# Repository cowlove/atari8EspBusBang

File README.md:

# Atari 8-bit ESP32 BusBang

```text
@@@@@@@@@@@@@@@@@@@@@@@@@@@@@@@@@@@@@@@@@@@@@@@@@@@@@@@@@@@@@@@@@@@@@@@@@@@@@@@
@     _   _             _  ___  _     _ _        _____ ____  ____ _________   @
@    / \ | |_ __ _ _ __(_)( _ )| |__ (_) |_     | ____/ ___||  _ \___ /___ \  @
@   / _ \| __/ _` | '__| |/ _ \| '_ \| | __|    |  _| \___ \| |_) ||_ \ __) | @
@  / ___ \ || (_| | |  | | (_) | |_) | | |_     | |___ ___) |  __/___) / __/  @
@ /_/   \_\__\__,_|_|  |_|\___/|_.__/|_|\__|    |_____|____/|_|  |____/_____| @
@                ____            ____                    _ _ _ _              @
@               | __ ) _   _ ___| __ )  __ _ _ __   __ _| | | | |             @
@               |  _ \| | | / __|  _ \ / _` | '_ \ / _` | | | | |             @
@               | |_) | |_| \__ \ |_) | (_| | | | | (_| |_|_|_|_|             @
@               |____/ \__,_|___/____/ \__,_|_| |_|\__, (_|_|_|_)             @
@                                                  |___/                      @
@@@@@@@@@@@@@@@@@@@@@@@@@@@@@@@@@@@@@@@@@@@@@@@@@@@@@@@@@@@@@@@@@@@@@@@@@@@@@@@
READY
█
```

## About the Project

Atari8EspBusBang uses a naked ESP32-S3 dev board to bit-bang the Atari 8-bit memory bus through the PBI port. The ESP32 has enough speed to handle the 6502's memory requests, overriding base memory and emulating extended memory, multi-bank cartridges, and SIO devices.  It implements a true software-defined PBI device.  The outside world, modern ideas, and high-level code all have direct access to the stock Atari system and memory at 960MB/sec.  

This started as a bus monitor for troubleshooting a flaky 800XL. Once it became clear that the ESP32 could also *respond* to bus requests, the project grew into a software-defined PBI device— and an ultimate extreme performance exercise on the ESP32. The bus-protocol loop runs bare-metal on the ESP32's second core; the first core handles utility tasks such as networking, PBI device logic, and flash disk-image access.

This idea pushes the ESP32 to its absolute performance limit, and the lower level parts of the project are intricate.  I'd like to eventually implement a simple module interface for adding functionality and trying ideas in easy code steps without needing to mess with or understand the low-level internals of this project.  

## Building the Hardware

The KiCad designs, parts list, PCB ordering notes, and assembly notes are in the [hardware README](hardware/README.md).  Total cost is about $20, and requires only through-hole soldering of headers. 

## Building the Firmware

The project depends on a specific pinned and lightly patched version of ESP-IDF v6.1, llvm-mos-sdk, and a few other tools.  Using the provided docker image is probably the easiest way to arrange for this. 

```
./tools/container/setup-build-env.sh container-runtime    # Install software needed to run podman  
./tools/container/container.sh pull                       # fetch/build docker image (6Gb/5min)
./tools/container/container.sh flash_spiffs /dev/ttyACM0  # first-time init of flash storage
./tools/container/container.sh flash /dev/ttyACM0         # build firmware and flash esp32 
```

Or you can install this all directly on your system and run esp-idf tools directly.  
```
./tools/container/setup-build-env.sh          # installs patched esp-idf,etc in ~/opt/ (6Gb/5min)
. ~/opt/atari8esp-idf-v6.1/export.sh          # set env to run esp-idf tools
./tools/flash_spiffs -p /dev/ttyACM0          # first-time init of flash storage 
idf.py --ccache flash -p /dev/ttyACM0         # build firmware and flash esp32
```

For the pinned Podman build environment, see [`tools/container/container.sh`](tools/container/container.sh) and [its README](tools/container/README.md).

## Contributing

Bug reports and focused contributions are welcome.  Please report issues with the environment setup scripts. 

## License

Distributed under GPL-2.0. See [LICENSE.txt](LICENSE.txt).

## Contact

Jim Evans — [jim@vheavy.com](mailto:jim@vheavy.com)

Project repository: <https://github.com/cowlove/atari8EspBusBang>

Project webpage: <http://cowlove.com/atari8EspBusBang/>

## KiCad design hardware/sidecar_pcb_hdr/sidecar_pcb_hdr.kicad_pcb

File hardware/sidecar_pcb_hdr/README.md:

# sidecar_pcb_hdr: one Sidecar board for every Atari, on a 2x25 bus header (draft)

The bare-module Sidecar board ([sidecar_pcb_xe](../sidecar_pcb_xe/)'s
layout, [sidecar_pcb_xl](../sidecar_pcb_xl/)'s circuit), with the
machine-specific edge connector replaced by a **2x25, 2.54 mm SMD socket**
(J1). A small adapter per machine plugs into it:

| Adapter | Machine | Its connector |
|---|---|---|
| [bus_adapter_pbi](../bus_adapter_pbi/) | 600XL, 800XL | the PBI card-edge socket (5530843-5), which the XL board carried |
| [bus_adapter_eci](../bus_adapter_eci/) | 130XE, 65XE | the cartridge + ECI fingers, which the XE board carried |

Why: one main board for both machine families (the XE board never got the
2026-11-18 re-spin; this one has it), no gold fingers or 50-way card-edge
socket on every spin of the expensive board, and insertion force and wear
go to a cheap part.

**Status: generated and autorouted, not reviewed.** A starting point.

## The bus header

`../tools/bus_header.py` holds the pinout; every generator imports it.
Header pin n is PBI pin n for every signal, so the PBI adapter is a straight
pass-through and this board keeps the XL board's net on each pin. The PBI's
three NC pins are GND on the header (12 grounds instead of 9). EXTDEC, CAS
and RAS pass through from the PBI and are open on the ECI adapter. Nothing
on this board uses them.

| Pin | Signal | Pin | Signal |
|---|---|---|---|
| 1 | GND | 2 | EXTSEL |
| 3 | A0 | 4 | A1 |
| 5 | A2 | 6 | A3 |
| 7 | A4 | 8 | A5 |
| 9 | A6 | 10 | GND |
| 11 | A7 | 12 | A8 |
| 13 | A9 | 14 | A10 |
| 15 | A11 | 16 | A12 |
| 17 | A13 | 18 | A14 |
| 19 | GND | 20 | A15 |
| 21 | D0 | 22 | D1 |
| 23 | D2 | 24 | D3 |
| 25 | D4 | 26 | D5 |
| 27 | D6 | 28 | D7 |
| 29 | GND | 30 | GND |
| 31 | PHI2 | 32 | GND |
| 33 | GND (PBI NC) | 34 | RESET |
| 35 | IRQ | 36 | READY |
| 37 | GND (PBI NC) | 38 | EXTDEC |
| 39 | GND (PBI NC) | 40 | REFRESH |
| 41 | CAS | 42 | GND |
| 43 | MPD | 44 | RAS |
| 45 | GND | 46 | READ |
| 47 | VCC50 | 48 | VCC50 |
| 49 | AUDIO | 50 | GND |

On this board, 47 is `VCC50_1` (to J6, as on the XL board) and 48 is
`VCC50_2` (unused). On the adapters, both are the Atari's 5 V.

## Mechanics

- **The stack.** The adapter stands in the Atari's connector. Its header
  (through-hole) is on its front face, and this board mates parallel to it,
  with J1 on this board's back. The modules face away from the Atari and the
  antennas point up, as on the XL board. `make_sidecar_hdr_pcb.py` turns
  J1 so that, seen from the front, socket pin n lies over header pin n on
  both adapters (it compares pad patterns and fails if none fits).
- **Position.** J1 is centred on a strip added below the XE board's body,
  so the board is 96 x 49 mm and the lower left corner is empty. The stack
  height (about 8.5 mm with a standard socket and header) and the fit
  behind each machine are unchecked.
- **Still to decide:**
  - **Keying.** Plain pins can be plugged in reversed or one row off, with
    5 V on the header. Options: a shrouded header on the adapters (the SMD
    socket must then fit inside the shroud), or a key pin (a header pin
    clipped and its socket hole plugged).
  - **Hold-downs.** The socket now carries the board's weight and every
    USB-C insertion at J9. Choose a socket part with pegs or board locks.
  - **Pitch.** 2.54 mm is cheap and sturdy. 2.0 mm would save about 12 mm
    of strip.

## Files

| File | |
|---|---|
| `sidecar_pcb_hdr.kicad_sch` | Generated by [`../tools/make_sidecar_hdr_schematic.py`](../tools/make_sidecar_hdr_schematic.py) from an XL schematic built with `--sidecar-usbc`: don't edit by hand |
| `sidecar_pcb_hdr.kicad_pcb` | Built by [`../tools/make_sidecar_hdr_pcb.py`](../tools/make_sidecar_hdr_pcb.py) from the XE board (all of its placement, J1 replaced, new outline), then autorouted |
| `sidecar_pcb_hdr.kicad_pro`, `.kicad_dru` | The project (copied from the XE board), and the XE board's J9 rule |

To rebuild (see [../AGENTS.md](../AGENTS.md)):

```
S=$(mktemp -d)
kicad-cli sch export netlist -o $S/sc.net hardware/espBusBangSidecar/espBusBangSidecar.kicad_sch
python3 hardware/tools/make_sidecar_xl_schematic.py hardware/espBusBangSidecar/espBusBangSidecar.kicad_sch \
    $S/sc.net hardware/symbols $S/xl-usbc.kicad_sch --sidecar-usbc
kicad-cli sch export netlist -o $S/xl-usbc.net $S/xl-usbc.kicad_sch
python3 hardware/tools/make_sidecar_hdr_schematic.py $S/xl-usbc.kicad_sch $S/xl-usbc.net \
    hardware/symbols hardware/sidecar_pcb_hdr/sidecar_pcb_hdr.kicad_sch
kicad-cli sch export netlist -o $S/hdr.net hardware/sidecar_pcb_hdr/sidecar_pcb_hdr.kicad_sch
(cd hardware/tools && /usr/bin/python3 make_sidecar_hdr_pcb.py ../sidecar_pcb_xe/sidecar_pcb_xe.kicad_pcb $S/hdr.net \
    ../bus_adapter_pbi/bus_adapter_pbi.kicad_pcb ../sidecar_pcb_hdr/sidecar_pcb_hdr.kicad_pcb)
hardware/tools/autoroute.sh hardware/sidecar_pcb_hdr/sidecar_pcb_hdr.kicad_pcb $S/hdr-routed.kicad_pcb 60
cp $S/hdr-routed.kicad_pcb hardware/sidecar_pcb_hdr/sidecar_pcb_hdr.kicad_pcb
```

The adapter boards come first (this script checks J1 against the PBI
adapter's header). `make_sidecar_hdr_pcb.py` imports helpers from
`make_bus_adapter_pcbs.py`, so run it from `hardware/tools`.

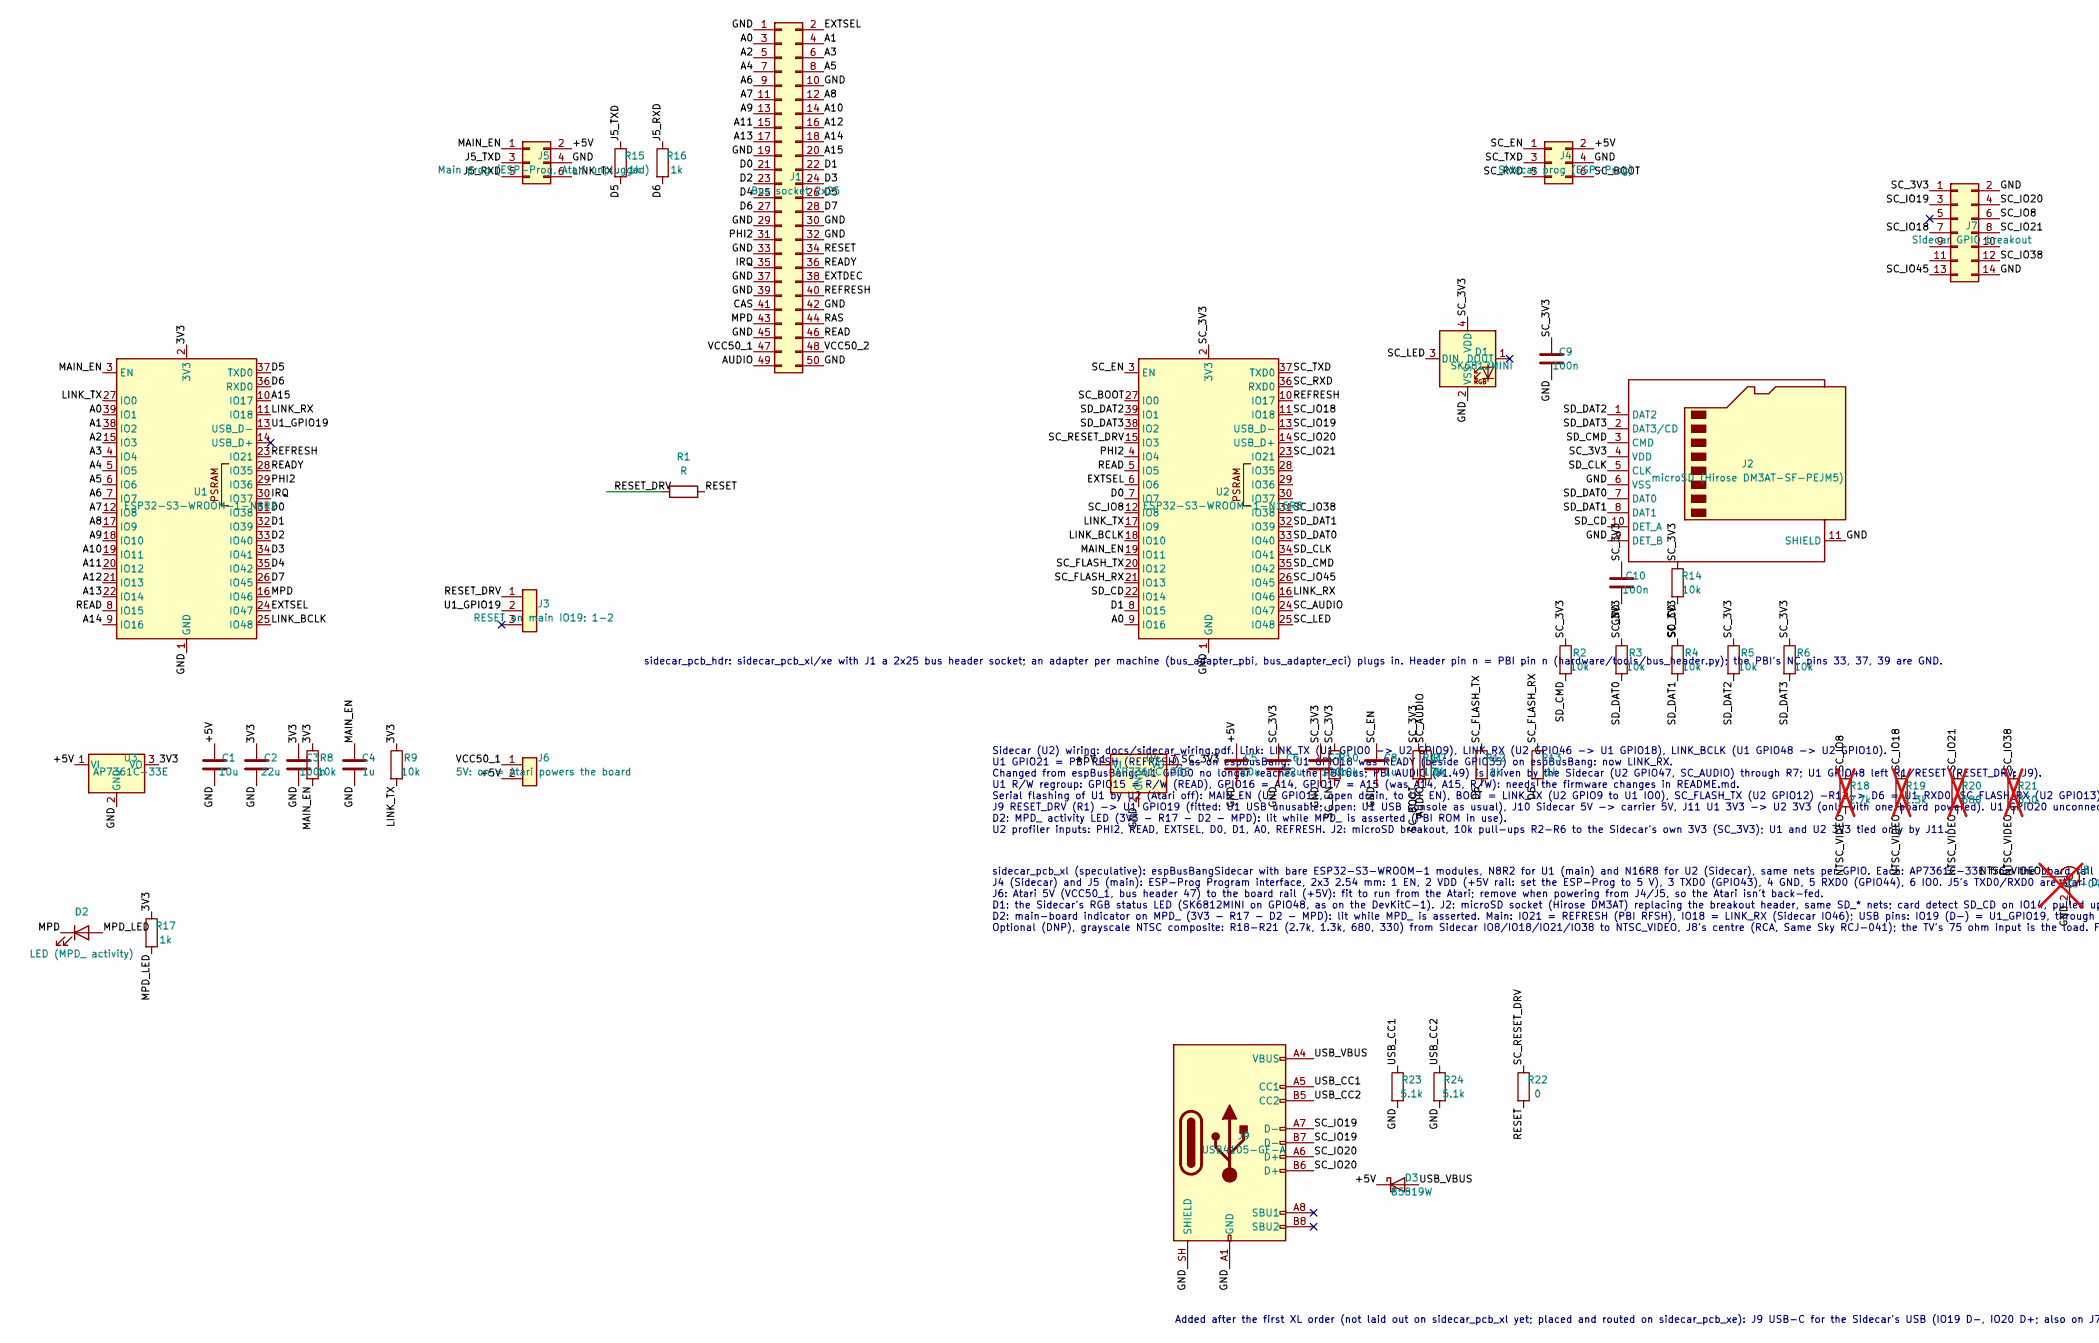
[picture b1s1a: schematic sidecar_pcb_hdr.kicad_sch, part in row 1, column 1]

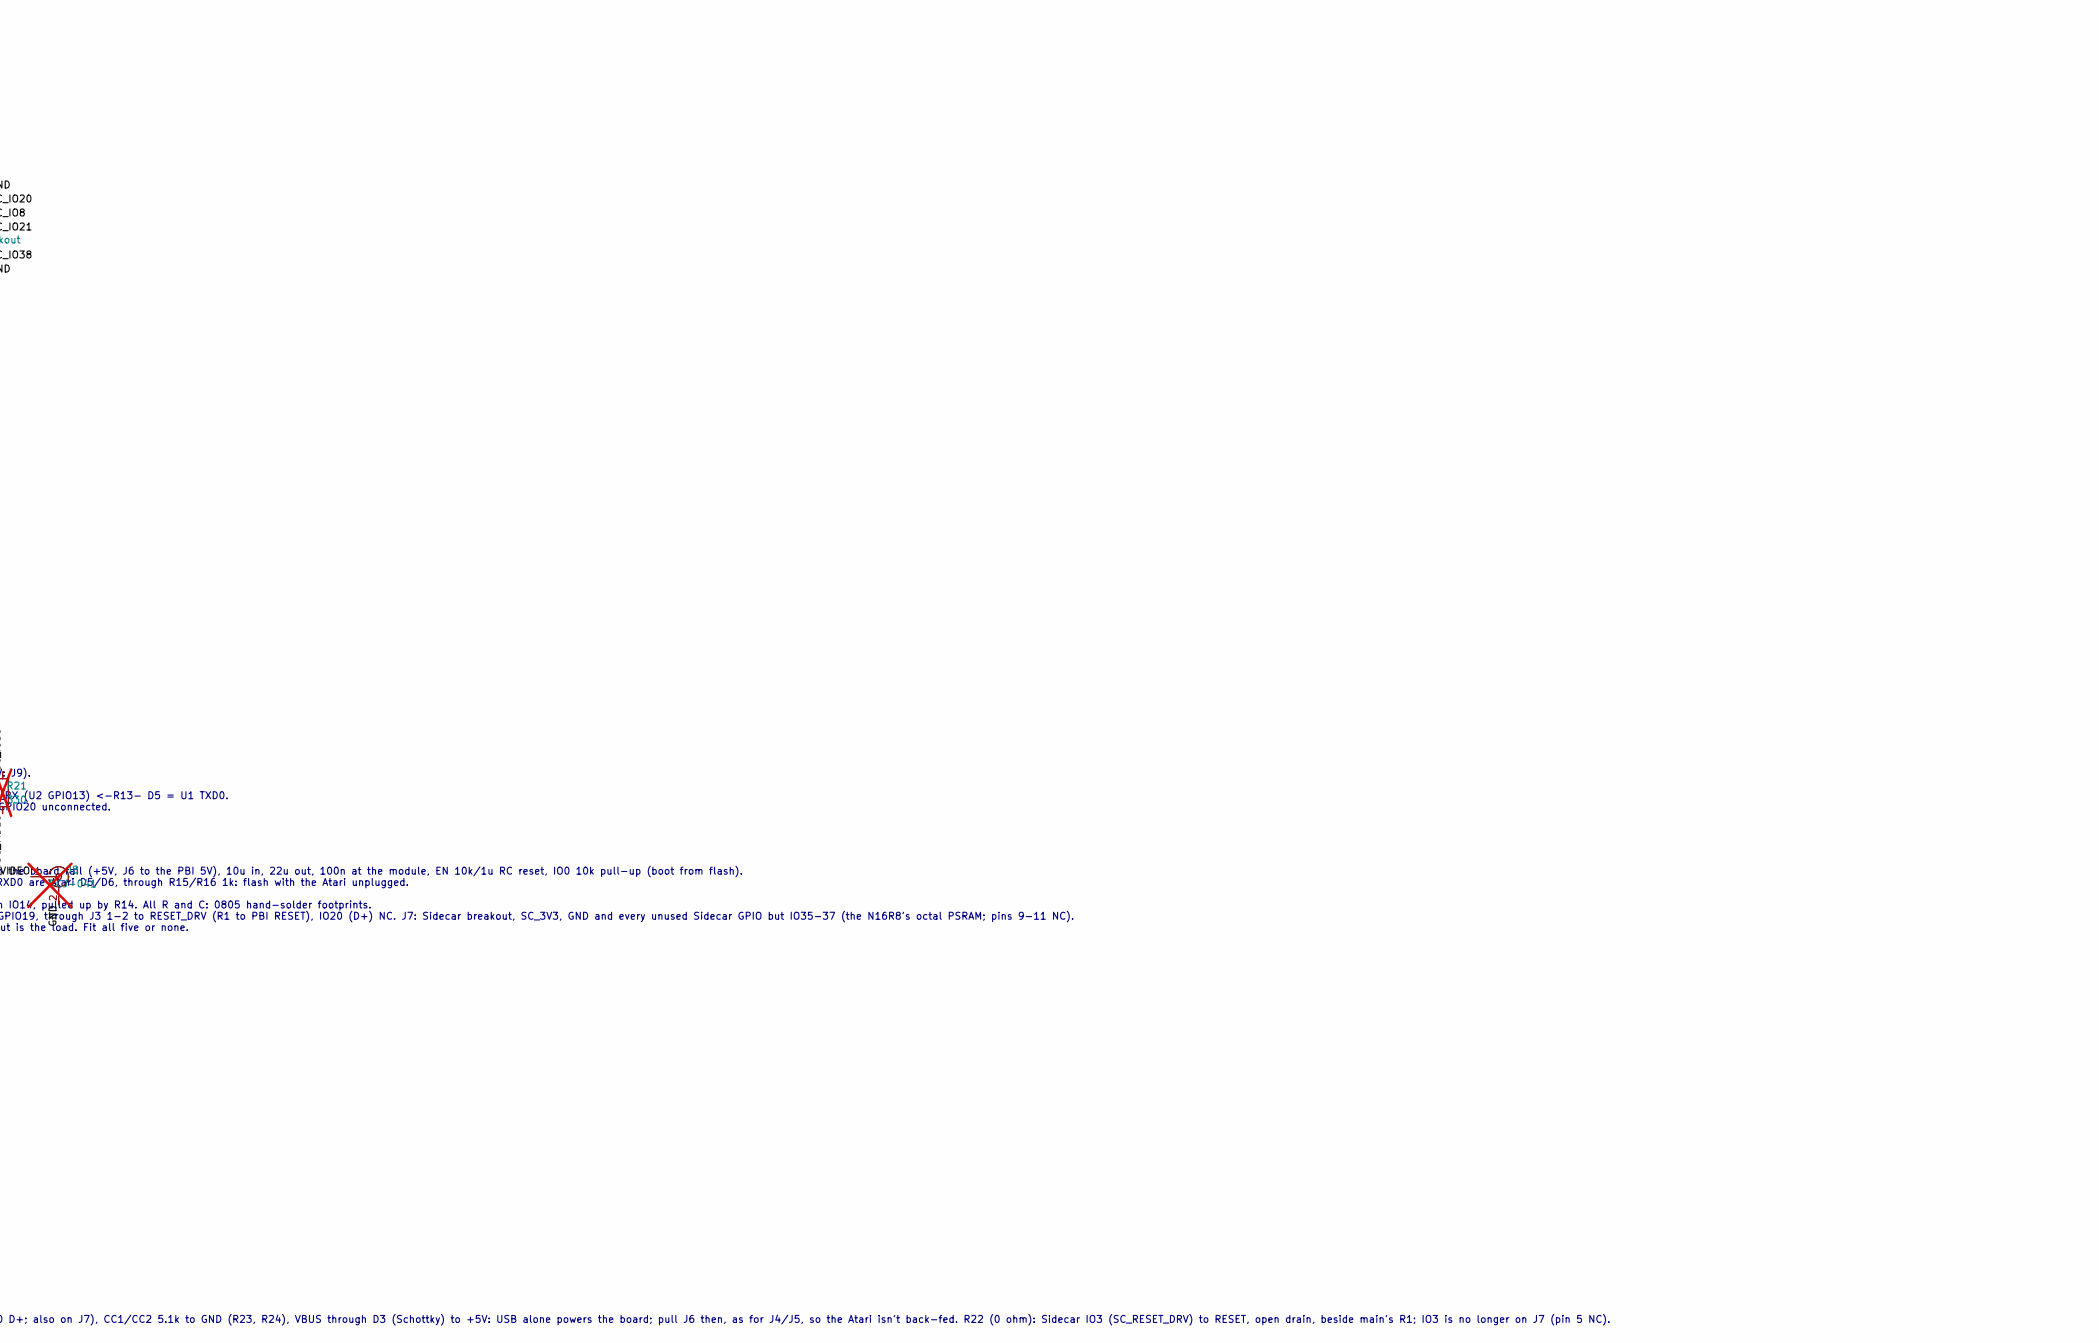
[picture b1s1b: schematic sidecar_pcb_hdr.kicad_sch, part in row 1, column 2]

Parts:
C1, C5: 10u; C_0805_2012Metric_Pad1.18x1.45mm_HandSolder
C2, C6: 22u; C_0805_2012Metric_Pad1.18x1.45mm_HandSolder
C3, C7, C9, C10: 100n; C_0805_2012Metric_Pad1.18x1.45mm_HandSolder
C4, C8: 1u; C_0805_2012Metric_Pad1.18x1.45mm_HandSolder
D1: SK6812MINI; LED_SK6812MINI_PLCC4_3.5x3.5mm_P1.75mm
D2: LED (MPD_ activity); LED_0805_2012Metric_Pad1.15x1.40mm_HandSolder
D3: B5819W; D_SOD-123
J1: Bus socket 2x25; PinSocket_2x25_P2.54mm_Vertical_SMD
J2: microSD (Hirose DM3AT-SF-PEJM5); microSD_HC_Hirose_DM3AT-SF-PEJM5
J3: RESET on main IO19: 1-2; PinHeader_1x03_P2.54mm_Vertical
J4: Sidecar prog (ESP-Prog); PinHeader_2x03_P2.54mm_Vertical
J5: Main prog (ESP-Prog, Atari unplugged); PinHeader_2x03_P2.54mm_Vertical
J6: 5V: on = Atari powers the board; PinHeader_1x02_P2.54mm_Vertical
J7: Sidecar GPIO breakout; PinHeader_2x07_P2.54mm_Vertical
J8: RCJ-041; RCA_SameSky_RCJ-04x_Horizontal; not fitted
J9: USB4105-GF-A; USB_C_Receptacle_GCT_USB4105-xx-A_16P_TopMnt_Horizontal
R1: R; R_0805_2012Metric_Pad1.20x1.40mm_HandSolder
R2, R3, R4, R5, R6, R8, R9, R10, R11, R14: 10k; R_0805_2012Metric_Pad1.20x1.40mm_HandSolder
R7, R12, R13, R15, R16, R17: 1k; R_0805_2012Metric_Pad1.20x1.40mm_HandSolder
R18: 2.7k; R_0805_2012Metric_Pad1.20x1.40mm_HandSolder; not fitted
R19: 1.3k; R_0805_2012Metric_Pad1.20x1.40mm_HandSolder; not fitted
R20: 680; R_0805_2012Metric_Pad1.20x1.40mm_HandSolder; not fitted
R21: 330; R_0805_2012Metric_Pad1.20x1.40mm_HandSolder; not fitted
R22: 0; R_0805_2012Metric_Pad1.20x1.40mm_HandSolder
R23, R24: 5.1k; R_0805_2012Metric_Pad1.20x1.40mm_HandSolder
U1: ESP32-S3-WROOM-1-N8R2; ESP32-S3-WROOM-1
U2: ESP32-S3-WROOM-1-N16R8; ESP32-S3-WROOM-1
U3, U4: AP7361C-33E; SOT-223-3_TabPin2

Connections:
/3V3: C2.1, C3.1, R8.1, R9.1, R17.1, U1.2 (3V3), U3.3 (VO)
/+5V: C1.1, C5.1, D3.1 (K), J4.2, J5.2, J6.2, U3.1 (VI), U4.1 (VI)
/A0: J1.3, U1.39 (IO1), U2.9 (IO16)
/A1: J1.4, U1.38 (IO2)
/A2: J1.5, U1.15 (IO3)
/A3: J1.6, U1.4 (IO4)
/A4: J1.7, U1.5 (IO5)
/A5: J1.8, U1.6 (IO6)
/A6: J1.9, U1.7 (IO7)
/A7: J1.11, U1.12 (IO8)
/A8: J1.12, U1.17 (IO9)
/A9: J1.13, U1.18 (IO10)
/A10: J1.14, U1.19 (IO11)
/A11: J1.15, U1.20 (IO12)
/A12: J1.16, U1.21 (IO13)
/A13: J1.17, U1.22 (IO14)
/A14: J1.18, U1.9 (IO16)
/A15: J1.20, U1.10 (IO17)
/AUDIO: J1.49, R7.2
/CAS: J1.41
/D0: J1.21, U1.31 (IO38), U2.7 (IO7)
/D1: J1.22, U1.32 (IO39), U2.8 (IO15)
/D2: J1.23, U1.33 (IO40)
/D3: J1.24, U1.34 (IO41)
/D4: J1.25, U1.35 (IO42)
/D5: J1.26, R13.2, R15.2, U1.37 (TXD0)
/D6: J1.27, R12.2, R16.2, U1.36 (RXD0)
/D7: J1.28, U1.26 (IO45)
/EXTDEC: J1.38
/EXTSEL: J1.2, U1.24 (IO47), U2.6 (IO6)
/GND: C1.2, C2.2, C3.2, C4.2, C5.2, C6.2, C7.2, C8.2, C9.2, C10.2, D1.2 (VSS), J1.1, J1.10, J1.19, J1.29, J1.30, J1.32, J1.33, J1.37, J1.39, J1.42, J1.45, J1.50, J2.6 (VSS), J2.9 (DET_B), J2.11 (SHIELD), J4.4, J5.4, J7.2, J7.14, J8.2 (Ext), J9.A1 (GND), J9.A12 (GND), J9.B1 (GND), J9.B12 (GND), J9.SH (SHIELD), R23.2, R24.2, U1.1 (GND), U1.40 (GND), U1.41 (GND), U2.1 (GND), U2.40 (GND), U2.41 (GND), U3.2 (GND), U4.2 (GND)
/IRQ: J1.35, U1.30 (IO37)
/J5_RXD: J5.5, R16.1
/J5_TXD: J5.3, R15.1
/LINK_BCLK: U1.25 (IO48), U2.18 (IO10)
/LINK_RX: U1.11 (IO18), U2.16 (IO46)
/LINK_TX: J5.6, R9.2, U1.27 (IO0), U2.17 (IO9)
/MAIN_EN: C4.1, J5.1, R8.2, U1.3 (EN), U2.19 (IO11)
/MPD: D2.1 (K), J1.43, U1.16 (IO46)
/MPD_LED: D2.2 (A), R17.2
/NTSC_VIDEO: J8.1 (In), R18.2, R19.2, R20.2, R21.2
/PHI2: J1.31, U1.29 (IO36), U2.4 (IO4)
/RAS: J1.44
/READ: J1.46, U1.8 (IO15), U2.5 (IO5)
/READY: J1.36, U1.28 (IO35)
/REFRESH: J1.40, U1.23 (IO21), U2.10 (IO17)
/RESET: J1.34, R1.2, R22.2
/RESET_DRV: J3.1, R1.1
/SC_3V3: C6.1, C7.1, C9.1, C10.1, D1.4 (VDD), J2.4 (VDD), J7.1, R2.1, R3.1, R4.1, R5.1, R6.1, R10.1, R11.1, R14.1, U2.2 (3V3), U4.3 (VO)
/SC_AUDIO: R7.1, U2.24 (IO47)
/SC_BOOT: J4.6, R11.2, U2.27 (IO0)
/SC_EN: C8.1, J4.1, R10.2, U2.3 (EN)
/SC_FLASH_RX: R13.1, U2.21 (IO13)
/SC_FLASH_TX: R12.1, U2.20 (IO12)
/SC_IO8: J7.6, R18.1, U2.12 (IO8)
/SC_IO18: J7.7, R19.1, U2.11 (IO18)
/SC_IO19: J7.3, J9.A7 (D-), J9.B7 (D-), U2.13 (USB_D-)
/SC_IO20: J7.4, J9.A6 (D+), J9.B6 (D+), U2.14 (USB_D+)
/SC_IO21: J7.8, R20.1, U2.23 (IO21)
/SC_IO38: J7.12, R21.1, U2.31 (IO38)
/SC_IO45: J7.13, U2.26 (IO45)
/SC_LED: D1.3 (DIN), U2.25 (IO48)
/SC_RESET_DRV: R22.1, U2.15 (IO3)
/SC_RXD: J4.5, U2.36 (RXD0)
/SC_TXD: J4.3, U2.37 (TXD0)
/SD_CD: J2.10 (DET_A), R14.2, U2.22 (IO14)
/SD_CLK: J2.5 (CLK), U2.34 (IO41)
/SD_CMD: J2.3 (CMD), R2.2, U2.35 (IO42)
/SD_DAT0: J2.7 (DAT0), R3.2, U2.33 (IO40)
/SD_DAT1: J2.8 (DAT1), R4.2, U2.32 (IO39)
/SD_DAT2: J2.1 (DAT2), R5.2, U2.39 (IO1)
/SD_DAT3: J2.2 (DAT3/CD), R6.2, U2.38 (IO2)
/U1_GPIO19: J3.2, U1.13 (USB_D-)
/USB_CC1: J9.A5 (CC1), R23.1
/USB_CC2: J9.B5 (CC2), R24.1
/USB_VBUS: D3.2 (A), J9.A4 (VBUS), J9.A9 (VBUS), J9.B4 (VBUS), J9.B9 (VBUS)
/VCC50_1: J1.47, J6.1
/VCC50_2: J1.48

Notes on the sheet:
Sidecar (U2) wiring: docs/sidecar_wiring.pdf. Link: LINK_TX (U1 GPIO0 -> U2 GPIO9), LINK_RX (U2 GPIO46 -> U1 GPIO18), LINK_BCLK (U1 GPIO48 -> U2 GPIO10). U1 GPIO21 = PBI RFSH (REFRESH), as on espBusBang. U1 GPIO18 was READY (beside GPIO35) on espBusBang: now LINK_RX. Changed from espBusBang: U1 GPI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
sidecar_pcb_xl (speculative): espBusBangSidecar with bare ESP32-S3-WROOM-1 modules, N8R2 for U1 (main) and N16R8 for U2 (Sidecar), same nets per GPIO. Each: AP7361C-33E from the board rail (+5V, J6 to the PBI 5V), 10u in, 22u out, 100n at the module, EN 10k/1u RC reset, IO0 10k pull-up (boot from f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
Added after the first XL order (not laid out on sidecar_pcb_xl yet; placed and routed on sidecar_pcb_xe): J9 USB-C for the Sidecar's USB (IO19 D-, IO20 D+; also on J7), CC1/CC2 5.1k to GND (R23, R24), VBUS through D3 (Schottky) to +5V: USB alone powers the board; pull J6 then, as for J4/J5, so the 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
sidecar_pcb_hdr: sidecar_pcb_xl/xe with J1 a 2x25 bus header socket; an adapter per machine (bus_adapter_pbi, bus_adapter_eci) plugs in. Header pin n = PBI pin n (hardware/tools/bus_header.py); the PBI's NC pins 33, 37, 39 are GND.

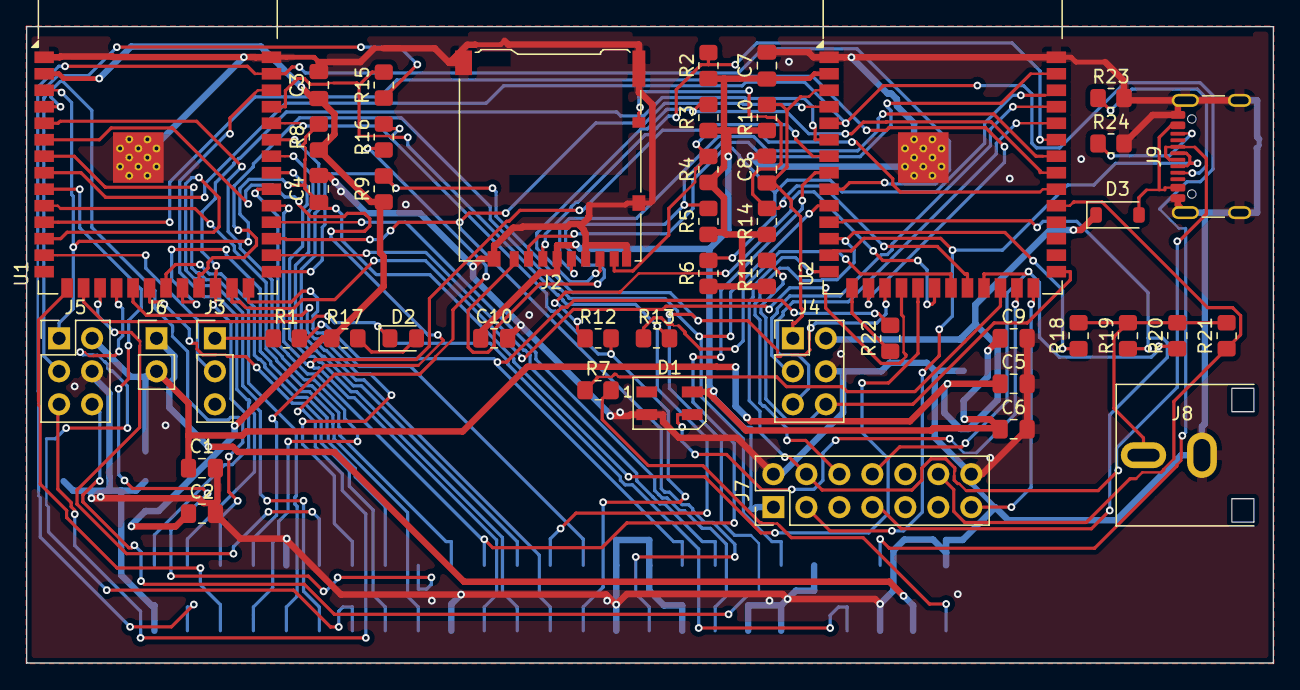
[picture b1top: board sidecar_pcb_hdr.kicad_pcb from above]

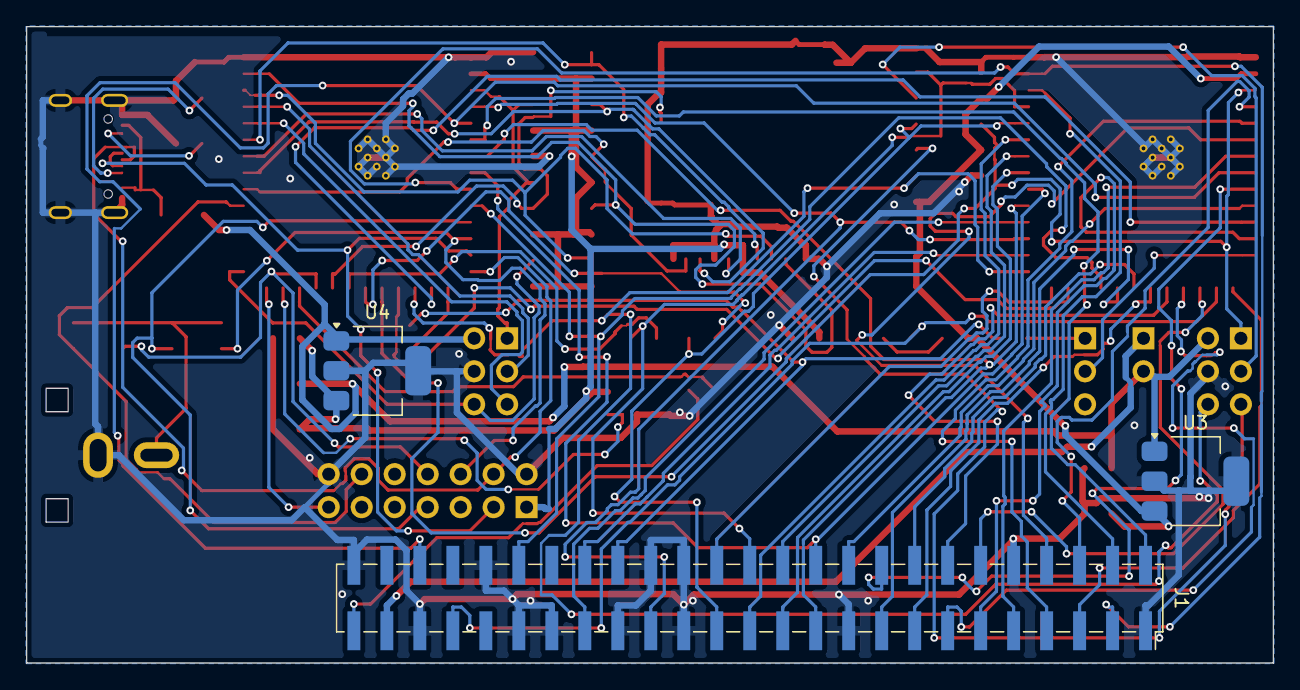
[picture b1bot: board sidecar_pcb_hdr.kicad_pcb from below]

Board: 2 copper layers, 96.0 x 49.0 mm, 50 parts (3 on the bottom side), 74 nets.

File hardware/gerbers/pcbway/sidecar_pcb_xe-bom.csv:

Item #,Designator,Qty,Manufacturer,Mfg Part #,Description / Value,Package/Footprint,Type,Your Instructions / Notes
1,"C1,C5",2,Samsung,CL21A106KAYNNNE,10uF 25V X5R MLCC,0805,SMD,
2,"C2,C6",2,Samsung,CL21A226MAQNNNE,22uF 25V X5R MLCC,0805,SMD,
3,"C3,C7,C9,C10",4,Samsung,CL21B104KBCNNNC,100nF 50V X7R MLCC,0805,SMD,
4,"C4,C8",2,Samsung,CL21B105KBFNNNE,1uF 50V X7R MLCC,0805,SMD,
5,D1,1,OPSCO,SK6812MINI,"RGB LED, integrated driver",PLCC4 3.5x3.5mm,SMD,
6,D2,1,Hubei KENTO,KT-0805G,Green LED,0805,SMD,"Any 0805 LED, colour free"
7,D3,1,Diodes Inc,B5819W-7-F,Schottky diode 40V 1A,SOD-123,SMD,
8,J2,1,Hirose,DM3AT-SF-PEJM5,"microSD socket, push-push",SMD,SMD,
9,J3,1,Generic,1x03 2.54mm male header,"3-pin 2.54mm male pin header, vertical",THT,THT,
10,"J4,J5",2,Generic,2x03 2.54mm male header,"6-pin 2.54mm male pin header, vertical",THT,THT,
11,J6,1,Generic,1x02 2.54mm male header,"2-pin 2.54mm male pin header, vertical",THT,THT,
12,J7,1,Generic,2x07 2.54mm male header,"14-pin 2.54mm male pin header, vertical",THT,THT,
13,J9,1,GCT,USB4105-GF-A,"USB-C receptacle, USB 2.0, 16 pin, top mount",SMD+THT,SMD,Mating face flush with the board edge
14,"R1,R22",2,UNI-ROYAL,0805W8F0000T5E,0 ohm resistor,0805,SMD,
15,"R2,R3,R4,R5,R6,R8,R9,R10,R11,R14",10,UNI-ROYAL,0805W8F1002T5E,10k 1% resistor,0805,SMD,
16,"R7,R12,R13,R15,R16,R17",6,UNI-ROYAL,0805W8F1001T5E,1k 1% resistor,0805,SMD,
17,"R23,R24",2,UNI-ROYAL,0805W8F5101T5E,5.1k 1% resistor (USB-C CC),0805,SMD,
18,U1,1,Espressif,ESP32-S3-WROOM-1-N8R2,"ESP32-S3 module, 8MB flash, 2MB PSRAM",SMD module,SMD,
19,U2,1,Espressif,ESP32-S3-WROOM-1-N16R8,"ESP32-S3 module, 16MB flash, 8MB octal PSRAM",SMD module,SMD,
20,"U3,U4",2,Diodes Inc,AP7361C-33E-13,3.3V 1A LDO regulator,SOT-223,SMD,Mounted on the bottom side

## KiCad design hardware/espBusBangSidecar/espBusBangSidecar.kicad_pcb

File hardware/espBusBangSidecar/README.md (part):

# espBusBangSidecar: the carrier with a Sidecar

A next-generation version of the [espBusBang](../espBusBang/) carrier with a
second ESP32-S3-DevKitC-1, the **Sidecar**, beside the main board. The
Sidecar talks to the main board over the I2S link and can run disk I/O, a bus
profiler, a microSD card and an audio output.

**Status: autorouted, not reviewed.** Placed by
[`../tools/place_sidecar_devkitc.py`](../tools/place_sidecar_devkitc.py) and
routed by [`../tools/autoroute.sh`](../tools/autoroute.sh) (see
[../AGENTS.md](../AGENTS.md)): no clearance errors, nothing unconnected,
schematic parity clean. Not checked by a human or ordered yet.

**Mounting, as on espBusBang:** J1 (PBI) is soldered in from the **back**,
the DevKitC sockets on the front, so the DevKitCs face out from the Atari:
there is no room for them on J1's side. (Both footprints sit on the front
layer in KiCad, as on espBusBang: don't flip J1.) U1 and J1 are exactly where
espBusBang has them; U2 sits beside U1, on the side away from J1's mounting
edge, and the headers (J2, J4, J5, J7, J9–J11) and the MPD_ LED (D2) run in a strip
beyond U2, outside the sockets. The small SMD resistors sit between the
DevKitCs' header rows, as R1 does on espBusBang: solder them before the
sockets. Board 71.3 × 63.8 mm; the right edge moved out 0.26 mm so U1's
outer pads clear the 0.5 mm edge clearance (espBusBang has 0.38 mm).

DRC leftovers: J1's pins 49/50 sit 0.38 mm from the top edge (as on
espBusBang); the DevKitC courtyards overlap the parts under them and J1
(intended); silkscreen overlaps from the DevKitC footprint's pin labels.

**The main board's firmware must change before this board can be used**: see
[Software changes required](#software-changes-required). The R/W pin moved.

## Files

| File | |
|---|---|
| `espBusBangSidecar.kicad_sch` | Generated: don't edit by hand |
| `espBusBangSidecar.kicad_pro`, `.kicad_pcb` | Board: from espBusBang's, updated by [`../tools/netlist_to_pcb.py`](../tools/netlist_to_pcb.py), placed and routed as above |
| [`../tools/make_sidecar_schematic.py`](../tools/make_sidecar_schematic.py) | Builds the schematic from `../espBusBang/atariEspBusBang3.kicad_sch` |
| [`../../docs/sidecar_wiring.pdf`](../../docs/sidecar_wiring.pdf) | The board-to-board wiring as a drawing (from [`../tools/sidecar_wiring.py`](../tools/sidecar_wiring.py)) |

To change the schematic, edit the script and regenerate:

```
python3 hardware/tools/make_sidecar_schematic.py \
    hardware/espBusBang/atariEspBusBang3.kicad_sch \
    hardware/espBusBangSidecar/espBusBangSidecar.kicad_sch
kicad-cli sch erc --severity-all -o erc.rpt hardware/espBusBangSidecar/espBusBangSidecar.kicad_sch
kicad-cli sch export netlist -o sidecar.net hardware/espBusBangSidecar/espBusBangSidecar.kicad_sch
```

ERC reports 83 items. None are new kinds of problem: the same classes the
original board has (labels on one-pin nets, no
PWR_FLAG, J1 pins of type "Unspecified"), plus "library not in the
configuration" when KiCad's library tables lack Espressif and the TE
connector.

## Parts added

Every resistor and LED, R1 from espBusBang included, uses KiCad's 0805
hand-solder footprints (longer pads, for an iron); only headers and
connectors are through-hole.

| Ref | Part | Footprint |
|---|---|---|
| U2 | ESP32-S3-DevKitC-1 (the Sidecar) | `Espressif:ESP32-S2-DevKitC-1`, as U1 |
| J2 | 1×8 header for a microSD breakout, in the card's pin order: DAT2, DAT3, CMD, 3V3, CLK, GND, DAT0, DAT1. An SDIO breakout (pins D0–D3, CMD, CLK) wires 1:1 and runs 4-bit. An SPI-only breakout works too, at about a quarter of the speed: CS → 2, DI/MOSI → 3, CLK → 5, DO/MISO → 7, GND → 6; if it has its own regulator, feed it 5 V (`SC_5V`) rather than pin 4's 3.3 V. The Sidecar tries SD mode, then SPI mode | `PinHeader_1x08_P2.54mm_Vertical` |
| R2–R6 | 10 k pull-ups to the Sidecar's 3V3 on SD CMD and DAT0–DAT3 | `R_0805_2012Metric_Pad1.20x1.40mm_HandSolder` |
| R7 | 1 k series resistor, Sidecar audio to the PBI audio input; sets the level, a starting guess | 0805 hand-solder |
| R12, R13 | 1 k series resistors in the Sidecar's flashing UART, to the main board's UART0 (Atari D6/D5) | 0805 hand-solder |
| J9, J10, J11 | 2-pin jumpers: RESET to main GPIO19 (USB D−), the Sidecar's 5V to the carrier's 5V, the two DevKitCs' 3V3 | `PinHeader_1x02_P2.54mm_Vertical` |
| J4 | Sidecar ESP-Prog header (2×3): 1 EN (`SC_EN`), 2 VDD (`SC_5V`), 3 TXD0 (GPIO43), 4 GND, 5 RXD0 (GPIO44), 6 IO0 (`SC_BOOT`), as on sidecar_pcb_xl. The DevKitC's own USB-UART is on the same TXD0/RXD0: use one or the other | `PinHeader_2x03_P2.54mm_Vertical` |
| J5, R15, R16 | Main ESP-Prog header: 1 EN (`MAIN_EN`), 2 VDD (`VCC50_1`), 3/5 TXD0/RXD0 through R15/R16 (1 k) to Atari D5/D6, 6 IO0 (`LINK_TX`). **Atari unplugged** (its UART is the data bus); an ESP-Prog at 5 V back-feeds the PBI 5 V, as the DevKitC's USB does | 2×3 header, 0805 R |
| J7 | Sidecar GPIO breakout (2×8): 1 `SC_3V3`, 2 GND, 3–15 the unused Sidecar GPIOs (19, 20, 3, 8, 14, 18, 21, 35, 36, 37, 38, 45, 48), 16 GND. On the DevKitC, GPIO19/20 are its USB port and GPIO48 its RGB LED; GPIO3 and 45 are straps | `PinHeader_2x08_P2.54mm_Vertical` |
| D2, R17 | MPD_ activity LED: main 3V3 → R17 (1 k) → D2 → `MPD`, lit while MPD_ is asserted | `LED_0805_2012Metric_Pad1.15x1.40mm_HandSolder`, 0805 R |

## The main board's link and RFSH pins (re-spin, 2026-11-18)

Hard-wired, with no jumpers:

| Main pin | Net | |
|---|---|---|
| GPIO18 | `LINK_RX`, from Sidecar GPIO46 | the link's RX. On espBusBang, GPIO18 is a second READY input (beside halt_'s GPIO35), never used by the firmware |
| GPIO21 | `REFRESH` (PBI RFSH) | `refresh_`, as on espBusBang, in every build |
| GPIO20 (USB D+) | unconnected | the USB port |

Until the re-spin, J3 selected GPIO21 (RFSH or link RX) and J8 put RFSH on
GPIO20; both are gone. The Sidecar's own RFSH input (GPIO17) is wired to
RFSH directly, as before.

## Fab orders and bench bodges

Two orders, tagged after the fact from history: `carrier-fab-2026-11-12`
(cc3606a; these are the boards in use) and `carrier-fab-2026-11-18`
(ac01011, the re-spin; not yet received). Neither connects the Sidecar to
PBI RESET, and the Nov 12 boards have no J11. The bodges in use:

- **One 3.3 V for both boards (Nov 12 boards, no J11):** each DevKitC's 3V3
  pin bent out of its socket and the two joined with a jumper, for a bench
  powered from the Sidecar's USB alone (joining the 5 V pins, J10, didn't
  work there). The Nov 18 boards have J11 for this.
- **The Sidecar driving the Atari's RESET (both orders):** a wire from J7
  pin 5 (`SC_IO3`, Sidecar GPIO3) to J9 pin 1 (`RESET_DRV`, R1's ESP end),
  J9 left open (fitted, it joins main's GPIO19, its USB D−, to the same
  net). The Sidecar app drives it open drain (`sidecar/main/atariReset.cpp`;
  console `atari [hold|release|reset [<ms>]]`): held from the Sidecar's
  start and whenever main (re)boots, released when main reports BOOT
  COMPLETE (SystemControl's BootComplete flag), so held all through
  diagnostic mode. The SMD XE board has it laid out (R22).

## J9–J11: reset and power jumpers

| Jumper | Joins | Fitted |
|---|---|---|
| J9 | R1's ESP end (`RESET_DRV`, R1 to PBI RESET) and main GPIO19, USB D− (`U1_GPIO19`) | the Atari's reset under the main board's control; main's USB port unusable (don't plug it in) |
| J10 | the carrier's 5 V (`VCC50_1`: PBI 5 V, the main DevKitC's 5V pin) and the Sidecar's 5V pin (`SC_5V`) | one 5 V for both boards |
| J11 | main's 3V3 (`3V3`) and the Sidecar's (`SC_3V3`) | one board runs from the other's 3.3 V regulator |

- **J9 open** (the default): the main DevKitC's USB port works as usual, and
  it's the console. **Fitted**: GPIO19 drives the Atari's RESET (firmware:
  open drain, through R1), and main's USB is off limits.
- **J10 open**: the Sidecar runs from its own USB, and nothing it's plugged
  into reaches the Atari's 5 V. **Fitted**: the Atari powers it too.
- **J11** is for when only one board has a supply: a DevKitC powered from its
  USB-JTAG port has no power on its 5V pin, so J10 can't share power then
  (found on the bench, 2026-11-17: the main board ran from the Sidecar's
  3V3). **Never fit it with both boards powered**: that parallels the two
  DevKitCs' 3.3 V regulators.

With J9 fitted this board is wired as sidecar_pcb_xl, except for the
DevKitC's own extras (its USB-serial bridge on main D5/D6, its LED).

## D2: MPD_ activity LED

The same indicator as sidecar_pcb_xl's (its README has the details): D2 lights
whenever MPD_ is asserted, which core 1 does while the 6502 runs the PBI ROM,
so it flickers with PBI requests. The main board only ever pulls MPD_ low, so
the LED can't cause a drive conflict. Fault blinking (only with the bus cold)
can be developed here for the bare-module board.

## Net changes on the main board (U1) vs espBusBang

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
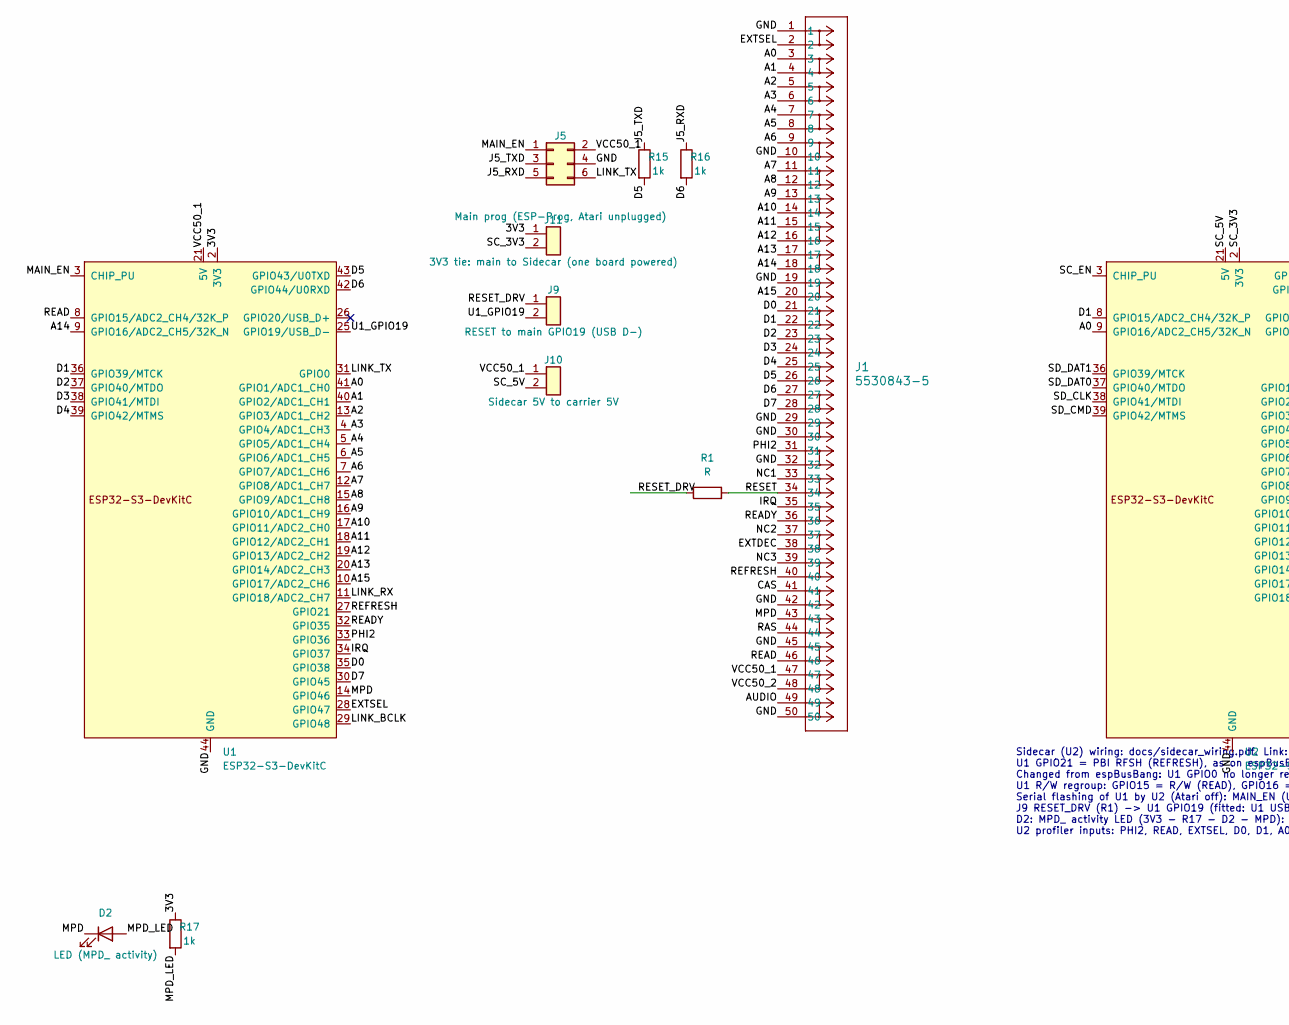
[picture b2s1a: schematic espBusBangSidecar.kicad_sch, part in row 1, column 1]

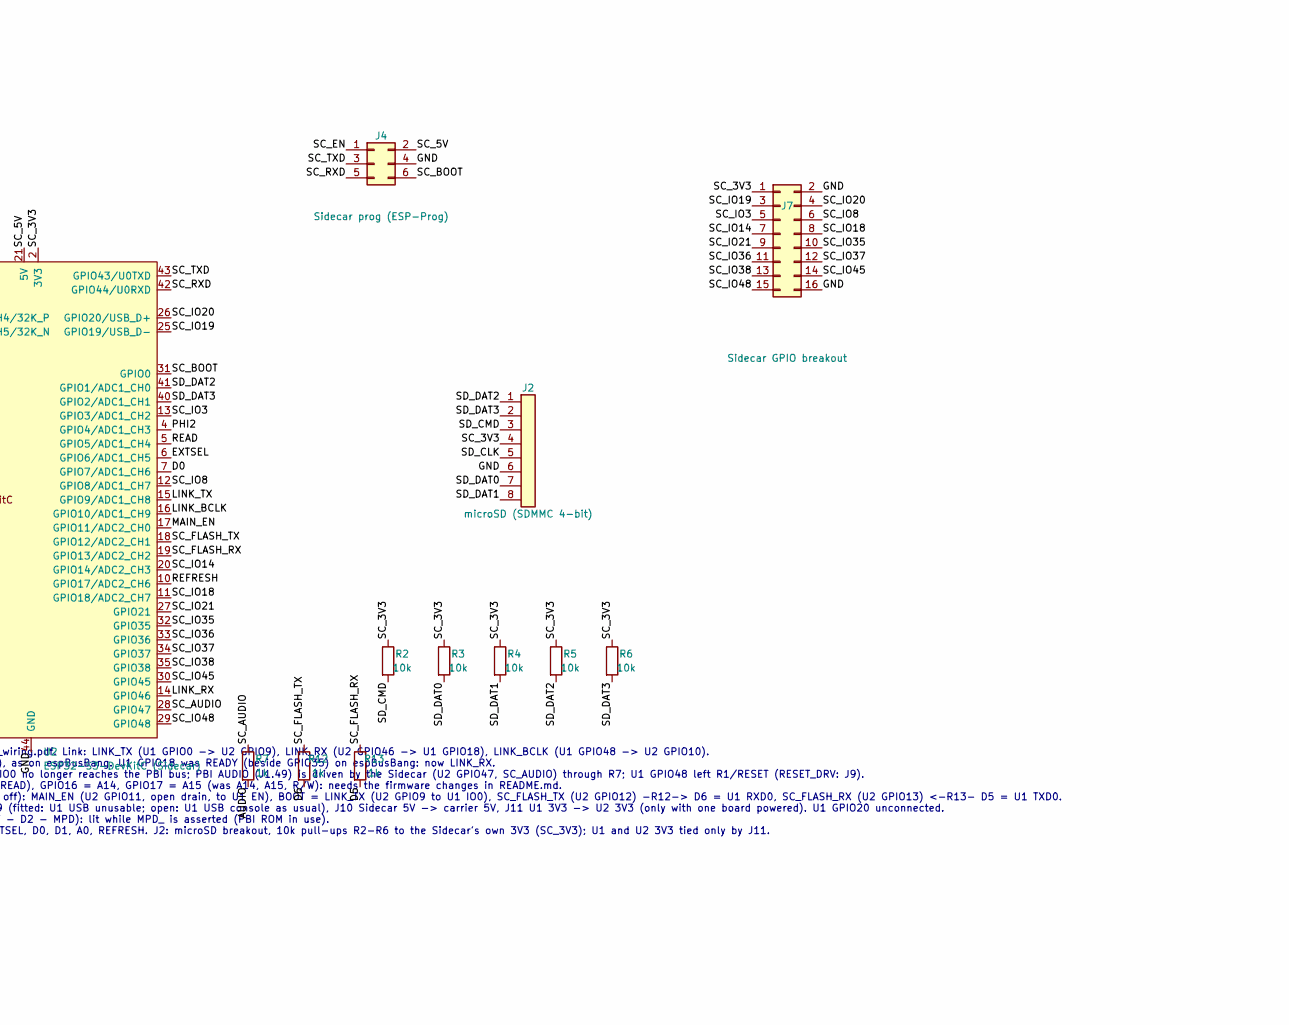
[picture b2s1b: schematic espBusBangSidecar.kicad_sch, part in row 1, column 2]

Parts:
D2: LED (MPD_ activity); LED_0805_2012Metric_Pad1.15x1.40mm_HandSolder
J1: 5530843-5; CONN50_5530843-5_TEC
J2: microSD (SDMMC 4-bit); PinHeader_1x08_P2.54mm_Vertical
J4: Sidecar prog (ESP-Prog); PinHeader_2x03_P2.54mm_Vertical
J5: Main prog (ESP-Prog, Atari unplugged); PinHeader_2x03_P2.54mm_Vertical
J7: Sidecar GPIO breakout; PinHeader_2x08_P2.54mm_Vertical
J9: RESET to main GPIO19 (USB D-); PinHeader_1x02_P2.54mm_Vertical
J10: Sidecar 5V to carrier 5V; PinHeader_1x02_P2.54mm_Vertical
J11: 3V3 tie: main to Sidecar (one board powered); PinHeader_1x02_P2.54mm_Vertical
R1: R; R_0805_2012Metric_Pad1.20x1.40mm_HandSolder
R2, R3, R4, R5, R6: 10k; R_0805_2012Metric_Pad1.20x1.40mm_HandSolder
R7, R12, R13, R15, R16, R17: 1k; R_0805_2012Metric_Pad1.20x1.40mm_HandSolder
U1: ESP32-S3-DevKitC; ESP32-S2-DevKitC-1
U2: ESP32-S3-DevKitC (Sidecar); ESP32-S2-DevKitC-1

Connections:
/3V3: J11.1, R17.1, U1.1 (3V3), U1.2 (3V3)
/A0: J1.3, U1.41 (GPIO1/ADC1_CH0), U2.9 (GPIO16/ADC2_CH5/32K_N)
/A1: J1.4, U1.40 (GPIO2/ADC1_CH1)
/A2: J1.5, U1.13 (GPIO3/ADC1_CH2)
/A3: J1.6, U1.4 (GPIO4/ADC1_CH3)
/A4: J1.7, U1.5 (GPIO5/ADC1_CH4)
/A5: J1.8, U1.6 (GPIO6/ADC1_CH5)
/A6: J1.9, U1.7 (GPIO7/ADC1_CH6)
/A7: J1.11, U1.12 (GPIO8/ADC1_CH7)
/A8: J1.12, U1.15 (GPIO9/ADC1_CH8)
/A9: J1.13, U1.16 (GPIO10/ADC1_CH9)
/A10: J1.14, U1.17 (GPIO11/ADC2_CH0)
/A11: J1.15, U1.18 (GPIO12/ADC2_CH1)
/A12: J1.16, U1.19 (GPIO13/ADC2_CH2)
/A13: J1.17, U1.20 (GPIO14/ADC2_CH3)
/A14: J1.18, U1.9 (GPIO16/ADC2_CH5/32K_N)
/A15: J1.20, U1.10 (GPIO17/ADC2_CH6)
/AUDIO: J1.49, R7.2
/CAS: J1.41
/D0: J1.21, U1.35 (GPIO38), U2.7 (GPIO7/ADC1_CH6)
/D1: J1.22, U1.36 (GPIO39/MTCK), U2.8 (GPIO15/ADC2_CH4/32K_P)
/D2: J1.23, U1.37 (GPIO40/MTDO)
/D3: J1.24, U1.38 (GPIO41/MTDI)
/D4: J1.25, U1.39 (GPIO42/MTMS)
/D5: J1.26, R13.2, R15.2, U1.43 (GPIO43/U0TXD)
/D6: J1.27, R12.2, R16.2, U1.42 (GPIO44/U0RXD)
/D7: J1.28, U1.30 (GPIO45)
/EXTDEC: J1.38
/EXTSEL: J1.2, U1.28 (GPIO47), U2.6 (GPIO6/ADC1_CH5)
/GND: J1.1, J1.10, J1.19, J1.29, J1.30, J1.32, J1.42, J1.45, J1.50, J2.6, J4.4, J5.4, J7.2, J7.16, U1.22 (GND), U1.23 (GND), U1.24 (GND), U1.44 (GND), U2.22 (GND), U2.23 (GND), U2.24 (GND), U2.44 (GND)
/IRQ: J1.35, U1.34 (GPIO37)
/J5_RXD: J5.5, R16.1
/J5_TXD: J5.3, R15.1
/LINK_BCLK: U1.29 (GPIO48), U2.16 (GPIO10/ADC1_CH9)
/LINK_RX: U1.11 (GPIO18/ADC2_CH7), U2.14 (GPIO46)
/LINK_TX: J5.6, U1.31 (GPIO0), U2.15 (GPIO9/ADC1_CH8)
/MAIN_EN: J5.1, U1.3 (CHIP_PU), U2.17 (GPIO11/ADC2_CH0)
/MPD: D2.1 (K), J1.43, U1.14 (GPIO46)
/MPD_LED: D2.2 (A), R17.2
/NC1: J1.33
/NC2: J1.37
/NC3: J1.39
/PHI2: J1.31, U1.33 (GPIO36), U2.4 (GPIO4/ADC1_CH3)
/RAS: J1.44
/READ: J1.46, U1.8 (GPIO15/ADC2_CH4/32K_P), U2.5 (GPIO5/ADC1_CH4)
/READY: J1.36, U1.32 (GPIO35)
/REFRESH: J1.40, U1.27 (GPIO21), U2.10 (GPIO17/ADC2_CH6)
/RESET: J1.34, R1.2
/RESET_DRV: J9.1, R1.1
/SC_3V3: J2.4, J7.1, J11.2, R2.1, R3.1, R4.1, R5.1, R6.1, U2.1 (3V3), U2.2 (3V3)
/SC_5V: J4.2, J10.2, U2.21 (5V)
/SC_AUDIO: R7.1, U2.28 (GPIO47)
/SC_BOOT: J4.6, U2.31 (GPIO0)
/SC_EN: J4.1, U2.3 (CHIP_PU)
/SC_FLASH_RX: R13.1, U2.19 (GPIO13/ADC2_CH2)
/SC_FLASH_TX: R12.1, U2.18 (GPIO12/ADC2_CH1)
/SC_IO3: J7.5, U2.13 (GPIO3/ADC1_CH2)
/SC_IO8: J7.6, U2.12 (GPIO8/ADC1_CH7)
/SC_IO14: J7.7, U2.20 (GPIO14/ADC2_CH3)
/SC_IO18: J7.8, U2.11 (GPIO18/ADC2_CH7)
/SC_IO19: J7.3, U2.25 (GPIO19/USB_D-)
/SC_IO20: J7.4, U2.26 (GPIO20/USB_D+)
/SC_IO21: J7.9, U2.27 (GPIO21)
/SC_IO35: J7.10, U2.32 (GPIO35)
/SC_IO36: J7.11, U2.33 (GPIO36)
/SC_IO37: J7.12, U2.34 (GPIO37)
/SC_IO38: J7.13, U2.35 (GPIO38)
/SC_IO45: J7.14, U2.30 (GPIO45)
/SC_IO48: J7.15, U2.29 (GPIO48)
/SC_RXD: J4.5, U2.42 (GPIO44/U0RXD)
/SC_TXD: J4.3, U2.43 (GPIO43/U0TXD)
/SD_CLK: J2.5, U2.38 (GPIO41/MTDI)
/SD_CMD: J2.3, R2.2, U2.39 (GPIO42/MTMS)
/SD_DAT0: J2.7, R3.2, U2.37 (GPIO40/MTDO)
/SD_DAT1: J2.8, R4.2, U2.36 (GPIO39/MTCK)
/SD_DAT2: J2.1, R5.2, U2.41 (GPIO1/ADC1_CH0)
/SD_DAT3: J2.2, R6.2, U2.40 (GPIO2/ADC1_CH1)
/U1_GPIO19: J9.2, U1.25 (GPIO19/USB_D-)
/VCC50_1: J1.47, J5.2, J10.1, U1.21 (5V)
/VCC50_2: J1.48

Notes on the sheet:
Sidecar (U2) wiring: docs/sidecar_wiring.pdf. Link: LINK_TX (U1 GPIO0 -> U2 GPIO9), LINK_RX (U2 GPIO46 -> U1 GPIO18), LINK_BCLK (U1 GPIO48 -> U2 GPIO10). U1 GPIO21 = PBI RFSH (REFRESH), as on espBusBang. U1 GPIO18 was READY (beside GPIO35) on espBusBang: now LINK_RX. Changed from espBusBang: U1 GPI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
